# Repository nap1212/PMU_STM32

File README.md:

# PMU Synchrophasor Dashboard

STM32F446RE (Nucleo) を使用した IEEE C37.118.1 準拠の PMU (Phasor Measurement Unit) 実装と、リアルタイム可視化ダッシュボードです。

---

## 概要

| 項目 | 内容 |
|---|---|
| MCU | STM32F446RE (Nucleo-F446RE) |
| GPS | Waveshare L76K GPS HAT |
| サンプリング周波数 | 2000 Hz |
| バッファサイズ | 200 サンプル (100 ms) |
| 対応系統周波数 | 50 Hz / 60 Hz |
| フェーザー推定 | LS法 (最小二乗) + DFT法 |
| 時刻同期 | GPS PPS (1秒パルス) による絶対フェーザー |

---

## ハードウェア構成

### 必要なもの

- STM32F446RE Nucleo ボード
- Waveshare L76K GPS HAT (または互換GPS モジュール)
- アナログ信号センサー (変換比 500:1)
- USB Type-A to Mini-B ケーブル
- ジャンパーワイヤー

### ピン接続

#### アナログ入力 (センサー)

```
交流電圧/電流
      │
   センサー (変換比 500:1)
      │
  DCバイアス回路 (目標: 1.65V = VDDA/2)
      │
   PA0 (Nucleo CN7 pin28) ← ADC1_IN0
```

#### GPS L76K HAT → Nucleo

```
L76K 40ピンヘッダー      Nucleo
─────────────────────────────────────
Pin 1  (3.3V)  ────→  3.3V (CN6 pin3)
Pin 6  (GND)   ────→  GND  (CN6 pin2)
Pin 7  (1PPS)  ────→  PA1  (CN7 pin24)  ← TIM5_CH2 入力キャプチャ
Pin 8  (TXD)   ────→  PA10 (CN10 pin33) ← USART1_RX
```

#### PC通信 (USB)

```
Nucleo USB ────→ PC (ST-Link 仮想COMポート, 115200 bps)
```

---

## ファームウェア機能

### 計測・解析

| 機能 | アルゴリズム |
|---|---|
| フェーザー推定 (相対) | LS法 (最小二乗) |
| フェーザー推定 (比較用) | DFT法 |
| **絶対フェーザー** | **GPS PPS 基準 UTC 同期** |
| 周波数推定 | ゼロクロス法 + 外れ値除外 |
| ROCOF | 周波数差分 |
| TVE | IEEE C37.118.1 準拠 (LS基準・DFT評価) |
| 高調波解析 | DFT 2次・3次 + THD |

### GPS同期

```
GPS PPS (1Hz) ──→ TIM5_CH2 入力キャプチャ
                      │
                  ppsCapture 記録 (90 MHz 分解能 ≈ 11 ns)
                      │
              バッファ先頭サンプル時刻との差分
                      │
              絶対位相 = 相対位相 − UTC基準コサイン位相
```

---

## ダッシュボード

Chrome / Edge でそのまま開けるシングルファイル HTML です。

```
pmu_dashboard.html をブラウザで開く
```

### 機能一覧

| パネル | 内容 |
|---|---|
| KPI カード | 周波数・振幅(LS/DFT)・相対位相・**絶対位相**・TVE・ROCOF・**GPS UTC/Lock** |
| 波形チャート | AC実測・LS推定・DFT推定 (200サンプルリアルタイム) |
| フェーザー図 | LS・DFT ベクトル描画 |
| 周波数トレンド | 直近60点 |
| TVE / THD / ROCOF トレンド | 直近60点 |
| アルゴリズム比較テーブル | LS vs DFT 履歴 |
| タイムスタンプログ | ミリ秒単位・GPS UTC 付き |
| CSV保存 | 全計測履歴をワンクリックでダウンロード |

### シリアル接続手順

1. Chrome または Edge でダッシュボードを開く (Firefox は WebSerial 非対応)
2. **「＋ デバイスを追加」** ボタンを押す
3. ブラウザのポート選択ダイアログで Nucleo の COM ポートを選択
4. **「接続」** ボタンを押す (115200 bps)

> デバイスパネルに `🔵 STM32 Nucleo` と表示されれば認識成功。  
> 接続すると自動でデモモードが停止し、実データに切り替わります。

---

## ビルド手順

### 1. 必要なもの

- STM32CubeIDE 1.14+
- STM32Cube FW_F4 V1.28+

### 2. ビルド

```
STM32CubeIDE でプロジェクトを開く
→ Project → Build Project
→ Run → Run
```

### 3. float printf 有効化 (初回のみ)

`Project → Properties → C/C++ Build → Settings → MCU GCC Linker → Miscellaneous → Other flags`

```
-u _printf_float
```

---

## シリアル出力フォーマット

### PLOT_MODE=0 (デフォルト: 波形)

```
AC:0.0012,LS_est:0.0011,DFT_est:0.0011   ← 200行
========================================
  PMU Synchrophasor Measurement Result
========================================
Frequency      : 50.012 Hz  [正常 50Hz]
ROCOF          : 0.0001 Hz/s
Abs Phase (LS) : -12.345 deg  [UTC基準]
GPS Lock       : LOCKED
UTC            : 12:34:56
TVE            : 0.234 %  [合格 <=1%]
...
```

### PLOT_MODE=1 (フェーザー情報)

```
Amp_LS:220.00,Amp_DFT:219.50,...,AbsPhase_LS:-12.345,UTC:12:34:56,GPS_LOCK:1
```

---

## ライセンス

MIT License

---

## 参考規格

- IEEE Std C37.118.1-2011: *IEEE Standard for Synchrophasor Measurements for Power Systems*
- NMEA 0183: GPS GPRMC センテンス

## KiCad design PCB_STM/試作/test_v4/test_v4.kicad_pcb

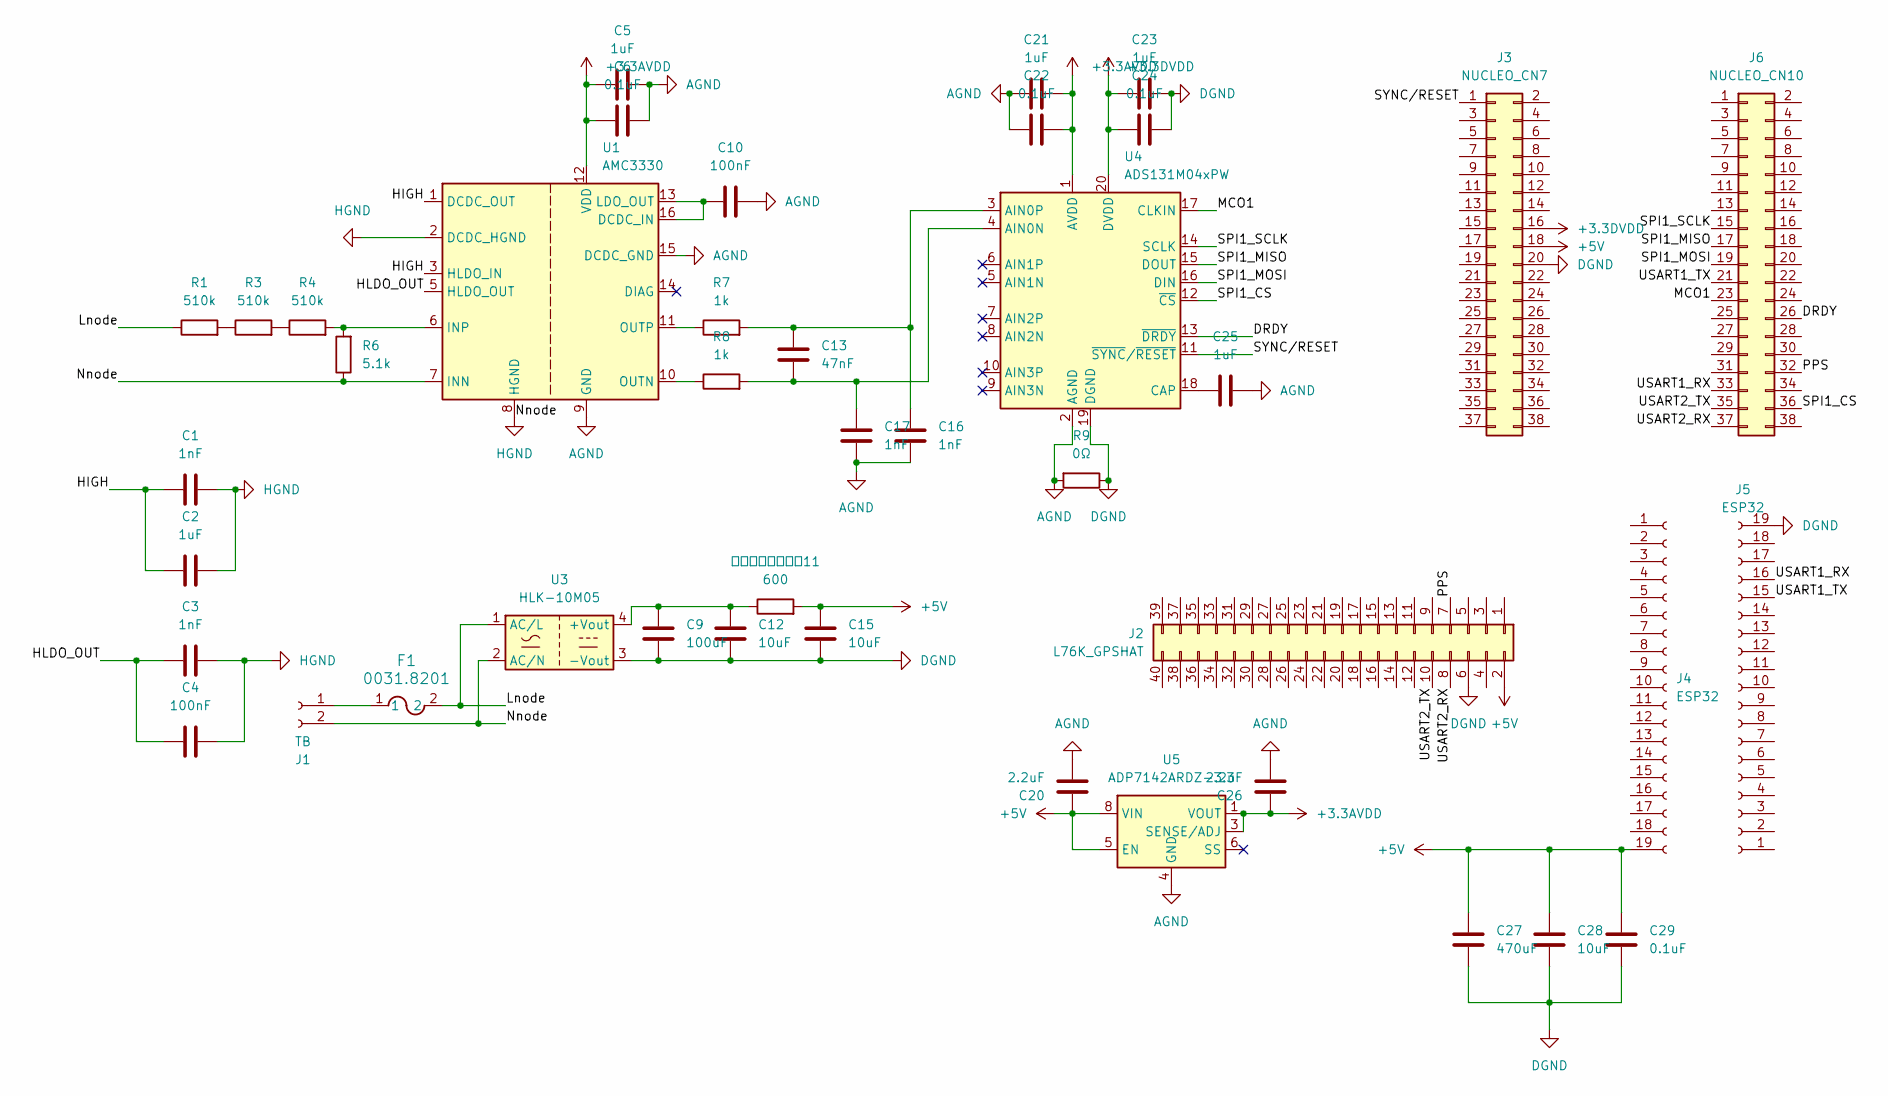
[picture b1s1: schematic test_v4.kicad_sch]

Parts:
C1, C3, C16, C17: 1nF; C_0805_2012Metric
C2, C5, C21, C23, C25: 1uF; C_0805_2012Metric
C4, C10: 100nF; C_0805_2012Metric
C6, C22, C24, C29: 0.1uF; C_0805_2012Metric
C9: 100uF; C_Radial_D6.3mm_H5.0mm_P2.50mm
C12, C15, C28: 10uF; C_0805_2012Metric
C13: 47nF; C_1206_3216Metric
C20, C26: 2.2uF; C_0805_2012Metric
C27: 470uF; C_Radial_D10.0mm_H12.5mm_P5.00mm
F1: 0031.8201; FUSE_0031.8201_SCH
J1: TB; Altech_AK300_1x02_P5.00mm_45-Degree
J2: L76K_GPSHAT; PinHeader_2x20_P2.54mm_Vertical
J3: NUCLEO_CN7; PinSocket_2x19_P2.54mm_Vertical
J4, J5: ESP32; PinSocket_1x19_P2.54mm_Vertical
J6: NUCLEO_CN10; PinSocket_2x19_P2.54mm_Vertical
R1, R3, R4: 510k; R_0805_2012Metric
R6: 5.1k; R_0805_2012Metric
R7, R8: 1k; R_0805_2012Metric
R9: 0Ω; R_0201_0603Metric
U1: AMC3330; SOIC-16W_7.5x10.3mm_P1.27mm
U3: HLK-10M05; Converter_ACDC_Hi-Link_HLK-10Mxx
U4: ADS131M04xPW; TSSOP-20_4.4x6.5mm_P0.65mm
U5: ADP7142ARDZ-3.3; SOIC-8-1EP_3.9x4.9mm_P1.27mm_EP2.29x3mm
フェライトビーズ11: 600; L_1206_3216Metric

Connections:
+3.3AVDD: C5.2, C6.2, C21.1, C22.1, C26.1, U1.12 (VDD), U4.1 (AVDD), U5.1 (VOUT), U5.2 (VOUT), U5.3 (SENSE/ADJ)
+3.3DVDD: C23.1, C24.1, J3.16, U4.20 (DVDD)
+5V: C15.1, C20.1, C27.1, C28.1, C29.1, J2.2, J3.18, J4.19 (Pin_19_19), U5.5 (EN), U5.7 (VIN), U5.8 (VIN), フェライトビーズ11.2
/DRDY: J6.26, U4.13 (~DRDY)
/HIGH: C1.1, C2.1, U1.1 (DCDC_OUT), U1.3 (HLDO_IN)
/HLDO_OUT: C3.1, C4.2, U1.5 (HLDO_OUT)
/Lnode: F1.2, R1.1, U3.1 (AC/L)
/MCO1: J6.23, U4.17 (CLKIN)
/PPS: J2.7, J6.32
/SPI1_CS: J6.36, U4.12 (~CS)
/SPI1_MISO: J6.17, U4.15 (DOUT)
/SPI1_MOSI: J6.19, U4.16 (DIN)
/SPI1_SCLK: J6.15, U4.14 (SCLK)
/SYNC/RESET: J3.1, U4.11 (~SYNC/~RESET)
/USART1_RX: J5.16, J6.33
/USART1_TX: J5.15, J6.21
/USART2_RX: J2.8, J6.37
/USART2_TX: J2.10, J6.35
AGND: C5.1, C6.1, C10.1, C16.2, C17.2, C20.2, C21.2, C22.2, C25.2, C26.2, R9.2, U1.9 (GND), U1.15 (DCDC_GND), U4.2 (AGND), U5.4 (GND), U5.9 (GND)
DGND: C9.2, C12.2, C15.2, C23.2, C24.2, C27.2, C28.2, C29.2, J2.6, J3.20, J5.19, R9.1, U3.3 (-Vout), U4.19 (DGND)
HGND: C1.2, C2.2, C3.2, C4.1, J1.2, R6.1, U1.2 (DCDC_HGND), U1.7 (INN), U1.8 (HGND), U3.2 (AC/N)
unnamed: F1.1, J1.1
unnamed: R1.2, R3.1
unnamed: R3.2, R4.1
unnamed: C10.2, U1.13 (LDO_OUT), U1.16 (DCDC_IN)
unnamed: R4.2, R6.2, U1.6 (INP)
unnamed: R8.1, U1.10 (OUTN)
unnamed: R7.1, U1.11 (OUTP)
unnamed: C9.1, C12.1, U3.4 (+Vout), フェライトビーズ11.1
unnamed: C13.2, C17.1, R8.2, U4.4 (AIN0N)
unnamed: C13.1, C16.1, R7.2, U4.3 (AIN0P)
unnamed: C25.1, U4.18 (CAP)

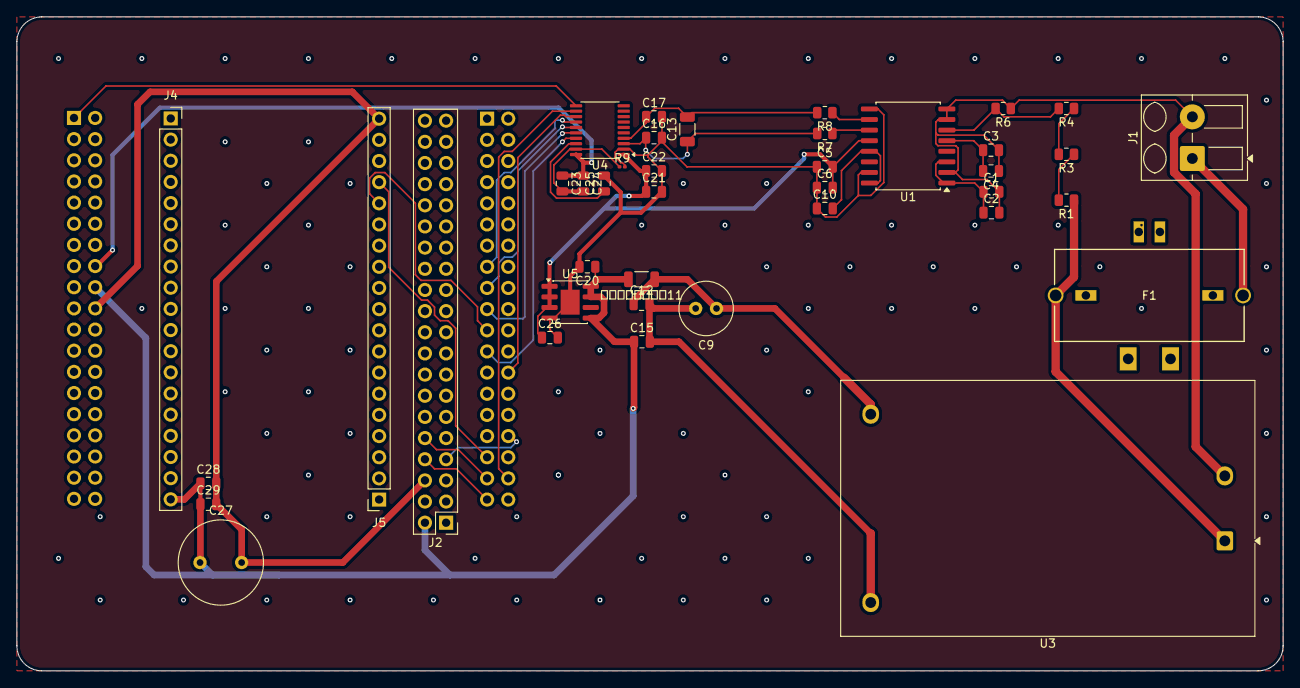
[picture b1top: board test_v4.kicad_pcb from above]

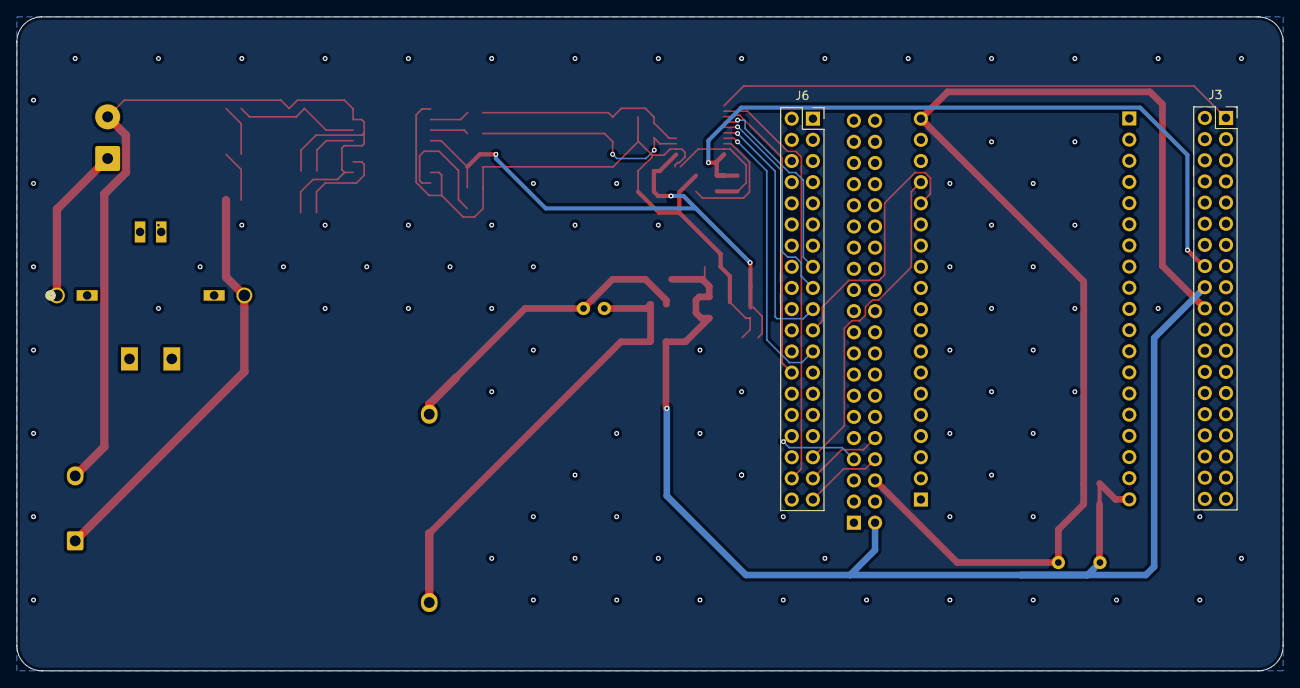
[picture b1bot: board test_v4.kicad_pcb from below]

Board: 2 copper layers, 152.0 x 78.5 mm, 42 parts (2 on the bottom side), 32 nets.

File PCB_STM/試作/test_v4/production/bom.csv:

Designator,Footprint,Quantity,Value,LCSC Part #
"C1, C16, C17, C3",0805,4,1nF,
"C10, C4",0805,2,100nF,
"C12, C15, C28",0805,3,10uF,
C13,1206,1,47nF,
"C2, C21, C23, C25, C5",0805,5,1uF,
"C20, C26",0805,2,2.2uF,
"C22, C24, C29, C6",0805,4,0.1uF,
C27,C_Radial_D10.0mm_H12.5mm_P5.00mm,1,470uF,
C9,C_Radial_D6.3mm_H5.0mm_P2.50mm,1,100uF,
F1,FUSE_0031.8201_SCH,1,0031.8201,
J1,Altech_AK300_1x02_P5.00mm_45-Degree,1,TB,
J2,PinHeader_2x20_P2.54mm_Vertical,1,L76K_GPSHAT,
J3,PinSocket_2x19_P2.54mm_Vertical,1,NUCLEO_CN7,
"J4, J5",PinSocket_1x19_P2.54mm_Vertical,2,ESP32,
J6,PinSocket_2x19_P2.54mm_Vertical,1,NUCLEO_CN10,
"R1, R3, R4",0805,3,510k,
R6,0805,1,5.1k,
"R7, R8",0805,2,1k,
R9,0201,1,0Ω,
U1,SOIC-16W_7.5x10.3mm_P1.27mm,1,AMC3330,
U3,Converter_ACDC_Hi-Link_HLK-10Mxx,1,HLK-10M05,
U4,TSSOP-20_4.4x6.5mm_P0.65mm,1,ADS131M04xPW,
U5,SOIC-8-1EP_3.9x4.9mm_P1.27mm_EP2.29x3mm,1,ADP7142ARDZ-3.3,
フェライトビーズ11,1206,1,600,

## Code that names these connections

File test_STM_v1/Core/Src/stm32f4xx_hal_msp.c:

/* USER CODE BEGIN Header */
/**
  ******************************************************************************
  * @file         stm32f4xx_hal_msp.c
  * @brief        This file provides code for the MSP Initialization
  *               and de-Initialization codes.
  ******************************************************************************
  * @attention
  *
  * Copyright (c) 2026 STMicroelectronics.
  * All rights reserved.
  *
  * This software is licensed under terms that can be found in the LICENSE file
  * in the root directory of this software component.
  * If no LICENSE file comes with this software, it is provided AS-IS.
  *
  ******************************************************************************
  */
/* USER CODE END Header */
/* Includes ------------------------------------------------------------------*/
#include "main.h"
/* USER CODE BEGIN Includes */

/* USER CODE END Includes */

/* Private typedef -----------------------------------------------------------*/
/* USER CODE BEGIN TD */

/* USER CODE END TD */

/* Private define ------------------------------------------------------------*/
/* USER CODE BEGIN Define */

/* USER CODE END Define */

/* Private macro -------------------------------------------------------------*/
/* USER CODE BEGIN Macro */

/* USER CODE END Macro */

/* Private variables ---------------------------------------------------------*/
/* USER CODE BEGIN PV */

/* USER CODE END PV */

/* Private function prototypes -----------------------------------------------*/
/* USER CODE BEGIN PFP */

/* USER CODE END PFP */

/* External functions --------------------------------------------------------*/
/* USER CODE BEGIN ExternalFunctions */

/* USER CODE END ExternalFunctions */

/* USER CODE BEGIN 0 */

/* USER CODE END 0 */
/**
  * Initializes the Global MSP.
  */
void HAL_MspInit(void)
{

  /* USER CODE BEGIN MspInit 0 */

  /* USER CODE END MspInit 0 */

  __HAL_RCC_SYSCFG_CLK_ENABLE();
  __HAL_RCC_PWR_CLK_ENABLE();

  /* System interrupt init*/

  /* USER CODE BEGIN MspInit 1 */

  /* USER CODE END MspInit 1 */
}

/**
  * @brief ADC MSP Initialization
  * This function configures the hardware resources used in this example
  * @param hadc: ADC handle pointer
  * @retval None
  */
void HAL_ADC_MspInit(ADC_HandleTypeDef* hadc)
{
  GPIO_InitTypeDef GPIO_InitStruct = {0};
  if(hadc->Instance==ADC1)
  {
    /* USER CODE BEGIN ADC1_MspInit 0 */

    /* USER CODE END ADC1_MspInit 0 */
    /* Peripheral clock enable */
    __HAL_RCC_ADC1_CLK_ENABLE();

    __HAL_RCC_GPIOA_CLK_ENABLE();
    /**ADC1 GPIO Configuration
    PA0-WKUP     ------> ADC1_IN0
    */
    GPIO_InitStruct.Pin = GPIO_PIN_0;
    GPIO_InitStruct.Mode = GPIO_MODE_ANALOG;
    GPIO_InitStruct.Pull = GPIO_NOPULL;
    HAL_GPIO_Init(GPIOA, &GPIO_InitStruct);

    /* ADC1 interrupt Init */
    HAL_NVIC_SetPriority(ADC_IRQn, 0, 0);
    HAL_NVIC_EnableIRQ(ADC_IRQn);
    /* USER CODE BEGIN ADC1_MspInit 1 */

    /* USER CODE END ADC1_MspInit 1 */

  }

}

/**
  * @brief ADC MSP De-Initialization
  * This function freeze the hardware resources used in this example
  * @param hadc: ADC handle pointer
  * @retval None
  */
void HAL_ADC_MspDeInit(ADC_HandleTypeDef* hadc)
{
  if(hadc->Instance==ADC1)
  {
    /* USER CODE BEGIN ADC1_MspDeInit 0 */

    /* USER CODE END ADC1_MspDeInit 0 */
    /* Peripheral clock disable */
    __HAL_RCC_ADC1_CLK_DISABLE();

    /**ADC1 GPIO Configuration
    PA0-WKUP     ------> ADC1_IN0
    */
    HAL_GPIO_DeInit(GPIOA, GPIO_PIN_0);

    /* ADC1 interrupt DeInit */
    HAL_NVIC_DisableIRQ(ADC_IRQn);
    /* USER CODE BEGIN ADC1_MspDeInit 1 */

    /* USER CODE END ADC1_MspDeInit 1 */
  }

}

/**
  * @brief TIM_Base MSP Initialization
  * This function configures the hardware resources used in this example
  * @param htim_base: TIM_Base handle pointer
  * @retval None
  */
void HAL_TIM_Base_MspInit(TIM_HandleTypeDef* htim_base)
{
  if(htim_base->Instance==TIM2)
  {
    /* USER CODE BEGIN TIM2_MspInit 0 */

    /* USER CODE END TIM2_MspInit 0 */
    /* Peripheral clock enable */
    __HAL_RCC_TIM2_CLK_ENABLE();
    /* TIM2 interrupt Init */
    HAL_NVIC_SetPriority(TIM2_IRQn, 0, 0);
    HAL_NVIC_EnableIRQ(TIM2_IRQn);
    /* USER CODE BEGIN TIM2_MspInit 1 */

    /* USER CODE END TIM2_MspInit 1 */

  }

}

/* USER CODE BEGIN 1 */
void HAL_TIM_IC_MspInit(TIM_HandleTypeDef* htim_ic)
{
  GPIO_InitTypeDef GPIO_InitStruct = {0};
  if(htim_ic->Instance == TIM5)
  {
    __HAL_RCC_TIM5_CLK_ENABLE();
    __HAL_RCC_GPIOA_CLK_ENABLE();
    /* PA1 → TIM5_CH2 (AF2) */
    GPIO_InitStruct.Pin       = GPIO_PIN_1;
    GPIO_InitStruct.Mode      = GPIO_MODE_AF_PP;
    GPIO_InitStruct.Pull      = GPIO_PULLDOWN;
    GPIO_InitStruct.Speed     = GPIO_SPEED_FREQ_LOW;
    GPIO_InitStruct.Alternate = GPIO_AF2_TIM5;
    HAL_GPIO_Init(GPIOA, &GPIO_InitStruct);
    HAL_NVIC_SetPriority(TIM5_IRQn, 1, 0);
    HAL_NVIC_EnableIRQ(TIM5_IRQn);
  }
}
/* USER CODE END 1 */

/**
  * @brief TIM_Base MSP De-Initialization
  * This function freeze the hardware resources used in this example
  * @param htim_base: TIM_Base handle pointer
  * @retval None
  */
void HAL_TIM_Base_MspDeInit(TIM_HandleTypeDef* htim_base)
{
  if(htim_base->Instance==TIM2)
  {
    /* USER CODE BEGIN TIM2_MspDeInit 0 */

    /* USER CODE END TIM2_MspDeInit 0 */
    /* Peripheral clock disable */
    __HAL_RCC_TIM2_CLK_DISABLE();

    /* TIM2 interrupt DeInit */
    HAL_NVIC_DisableIRQ(TIM2_IRQn);
    /* USER CODE BEGIN TIM2_MspDeInit 1 */

    /* USER CODE END TIM2_MspDeInit 1 */
  }

}

/**
  * @brief UART MSP Initialization
  * This function configures the hardware resources used in this example
  * @param huart: UART handle pointer
  * @retval None
  */
void HAL_UART_MspInit(UART_HandleTypeDef* huart)
{
  GPIO_InitTypeDef GPIO_InitStruct = {0};
  if(huart->Instance==USART2)
  {
    /* USER CODE BEGIN USART2_MspInit 0 */

    /* USER CODE END USART2_MspInit 0 */
    /* Peripheral clock enable */
    __HAL_RCC_USART2_CLK_ENABLE();

    __HAL_RCC_GPIOA_CLK_ENABLE();
    /**USART2 GPIO Configuration
    PA2     ------> USART2_TX
    PA3     ------> USART2_RX
    */
    GPIO_InitStruct.Pin = GPIO_PIN_2|GPIO_PIN_3;
    GPIO_InitStruct.Mode = GPIO_MODE_AF_PP;
    GPIO_InitStruct.Pull = GPIO_NOPULL;
    GPIO_InitStruct.Speed = GPIO_SPEED_FREQ_VERY_HIGH;
    GPIO_InitStruct.Alternate = GPIO_AF7_USART2;
    HAL_GPIO_Init(GPIOA, &GPIO_InitStruct);

    /* USER CODE BEGIN USART2_MspInit 1 */

    /* USER CODE END USART2_MspInit 1 */

  }

  if(huart->Instance==USART1)
  {
    __HAL_RCC_USART1_CLK_ENABLE();
    __HAL_RCC_GPIOA_CLK_ENABLE();
    /* PA10 → USART1_RX (AF7) */
    GPIO_InitStruct.Pin       = GPIO_PIN_10;
    GPIO_InitStruct.Mode      = GPIO_MODE_AF_PP;
    GPIO_InitStruct.Pull      = GPIO_PULLUP;
    GPIO_InitStruct.Speed     = GPIO_SPEED_FREQ_VERY_HIGH;
    GPIO_InitStruct.Alternate = GPIO_AF7_USART1;
    HAL_GPIO_Init(GPIOA, &GPIO_InitStruct);
    HAL_NVIC_SetPriority(USART1_IRQn, 2, 0);
    HAL_NVIC_EnableIRQ(USART1_IRQn);
  }

}

/**
  * @brief UART MSP De-Initialization
  * This function freeze the hardware resources used in this example
  * @param huart: UART handle pointer
  * @retval None
  */
void HAL_UART_MspDeInit(UART_HandleTypeDef* huart)
{
  if(huart->Instance==USART2)
  {
    /* USER CODE BEGIN USART2_MspDeInit 0 */

    /* USER CODE END USART2_MspDeInit 0 */
    /* Peripheral clock disable */
    __HAL_RCC_USART2_CLK_DISABLE();

    /**USART2 GPIO Configuration
    PA2     ------> USART2_TX
    PA3     ------> USART2_RX
    */
    HAL_GPIO_DeInit(GPIOA, GPIO_PIN_2|GPIO_PIN_3);

    /* USER CODE BEGIN USART2_MspDeInit 1 */

    /* USER CODE END USART2_MspDeInit 1 */
  }

}

/* USER CODE BEGIN 1 */

/* USER CODE END 1 */
